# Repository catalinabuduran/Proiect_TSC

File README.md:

# OpenBook - Open Source e-Book Reader

## Functionalitate hardware

Dispozitivul OpenBook integreaza o serie de module si componente menite sa ofere o experienta completa pentru citirea cartilor in format digital, precum si extinderea functiilor prin senzori si periferice externe. Hardware-ul este compus din mai multe blocuri functionale, fiecare avand rolul. Am integrat atat componente de interfata (buton, ecran), cat si senzori, circuite de alimentare si protectie.

### Componente principale:

## Dispozitivul este compus dintr-un set de componente atent alese pentru a oferi un echilibru perfect intre performanta, consum redus de energie si modularitate. ##
|  Componenta            | Descriere                                                      |
|---------------------------|----------------------------------------------------------------|
|ESP32-C6-WROOM-1-N8  | MCU principal cu WiFi 6, BLE 5.0, SPI, I2C, UART               |
|E-paper Display | Afisaj ultra-low power, interfata SPI                          |
|SD Card         | Stocare pentru fisiere e-book si configurari                   |
|NOR Flash 64MB  | Memorie suplimentara pentru firmware si date                   |
|RTC-DS3231SN | Ceas in timp real, exact si stabil                             |
|    BME688   | Senzor de mediu complet: T, RH, presiune, VOC                  |
| MAX17048    | Masurare SoC baterie, tensiune, temperatura                  |
|MCP73831     | Incarcare LiPo simpla si eficienta                           |
|XC6220 LDO      | Regulare 5V -> 3.3V cu zgomot scazut                            |
|USB-C           | Alimentare + flash firmware + protectie ESD                   |
|Qwiic/Stemma QT | Extensie rapida pentru senzori I2C                            |

---

## Pinout ESP32-C6

Mai jos este un rezumat al pinilor folositi pe microcontroller, cu functiile si componenta asociata:

| GPIO  | Componenta        | Functie                     |
|--------|--------------------|-----------------------------|
| EN     | Buton Reset        | Reset hardware              |
| IO0    | RTC                | INT_RTC (interupt RTC)      |
| IO1    | RTC                | 32KHz output                |
| IO2    | SD Card            | MISO                        |
| IO3    | E-paper Display    | EPD_BUSY                    |
| IO4    | SD Card            | SS_SD (chip select)         |
| IO5    | E-paper Display    | EPD_DC                      |
| IO6    | SPI Shared         | SCK                         |
| IO7    | SPI Shared         | MOSI                        |
| IO8    | GPIO               | Utilizare generica          |
| IO9    | Boot Button        | Mod programare              |
| IO10   | E-paper Display    | EPD_CS                      |
| IO11   | NOR Flash          | FLASH_CS                    |
| IO12   | USB Interface      | USB_D-                      |
| IO13   | USB Interface      | USB_D+                      |
| IO15   | Buton Change       | Detectare schimbare         |
| IO16   | UART               | TX (debug serial)           |
| IO17   | UART               | RX (debug serial)           |
| IO18   | RTC                | RTC_RST                     |
| IO19   | MAX17048           | I2C_PW (alimentare I2C)     |
| IO20   | E-paper Display    | EPD_3V3_C (power control)   |
| IO21   | I2C Shared         | SDA                         |
| IO22   | I2C Shared         | SCL                         |
| IO23   | E-paper Display    | EPD_RST                     |

---

## Arhitectura si comunicatii

- **SPI Bus** este partajat intre: SD Card, E-paper Display, NOR Flash
- **I2C Bus** este partajat intre: RTC, BME688, MAX17048, Qwiic port
- **UART** este utilizat pentru debugging (TX/RX)
- **USB-C** foloseste GPIO dedicate pentru DP/DM si incarcare

---

# BOM TSC - Lista de componente

| Nr. piesa | Nume piesa | Site | Datasheet |
| --- | --- | --- | --- |
| 1 | BOOT_BUTON | https://www.snapeda.com/parts/EVQP7L01P/Panasonic%20Electronic%20Components/view-part/?welcome=home | https://www.snapeda.com/parts/EVQP7L01P/Panasonic/datasheet/ |
| 2 | C1, C1_BAT, C1_BAT2, C2,C2_BAT,C3,C4,C4_USB, C5, C5_USB, C6, C7, C8, C9,C10 | https://componentsearchengine.com/part-view/CC0402MRX5R5BB106/YAGEO | https://componentsearchengine.com/Datasheets/2/CC0402MRX5R5BB106.pdf |
| 3 | C10_SUPERCAR | https://industry.panasonic.com/global/en/products/control/switch/light-touch/number/evqpuj02k | https://industry.panasonic.com/global/en/downloads?tab=catalog&small_g_cd=203&part_no=EVQPUJ02K |
| 4 | CHANGE_BUTTON | https://www.snapeda.com/parts/EVQP7L01P/Panasonic%20Electronic%20Components/view-part/?welcome=home | https://www.snapeda.com/parts/EVQP7L01P/Panasonic/datasheet/ |
| 5 | C_DELAY | https://componentsearchengine.com/part-view/CC0402MRX5R5BB106/YAGEO | https://componentsearchengine.com/Datasheets/2/CC0402MRX5R5BB106.pdf |
| 6 | D1 | https://www.snapeda.com/parts/USBLC6-2SC6Y/STMicroelectronics/view-part/?ref=eda | https://www.snapeda.com/parts/USBLC6-2SC6Y/STMicroelectronics/view-part/?ref=eda |
| 7 | EPD_C1,EPD_C2, EPD_C3, EPD_C4, EPD_C5,EPD_C6,EPD_C7,EPD_C8,EPD_C9,EPD_C10,EPD_C11,EPD_C12 | https://componentsearchengine.com/part-view/CC0402MRX5R5BB106/YAGEO | https://componentsearchengine.com/Datasheets/2/CC0402MRX5R5BB106.pdf |
| 8 | IC1 | https://componentsearchengine.com/part-view/BD5229G-TR/ROHM%20Semiconductor | https://datasheet.datasheetarchive.com/originals/distributors/Datasheets_SAMA/f2b9741ef86007909f138d561a359946.pdf |
| 9 | IC4 | https://componentsearchengine.com/part-view/XC6220A331MR-G/Torex | https://product.torexsemi.com/system/files/series/xc6220.pdf |
| 10 | J1 | https://componentsearchengine.com/part-view/FH34SRJ-24S-0.5SH(99)/Hirose | https://www.hirose.com/en/product/document?clcode=CL0580-1255-6-99&productname=FH34SRJ-24S-0.5SH(99)&series=FH34SRJ&documenttype=2DDrawing&lang=en&documentid=0000990903 |
| 11 | J2 | https://componentsearchengine.com/part-view/USB4110-GF-A/GCT%20(GLOBAL%20CONNECTOR%20TECHNOLOGY) | https://gct.co/files/drawings/usb4110.pdf |
| 12 | J3,J4 | https://www.snapeda.com/parts/PRT-14417/SparkFun/view-part/ | https://www.snapeda.com/parts/PRT-14417/SparkFun%20Electronics/datasheet/ |
| 13 | MCP73831 | https://ro.mouser.com/ProductDetail/Microchip-Technology/MCP73831T-2ACI-OT?qs=yUQqVecv4qvbBQBGbHx0Mw%3D%3D&utm_id=20109199409&utm_source=google&utm_medium=cpc&utm_marketing_tactic=emeacorp&gad_source=1&gbraid=0AAAAADn_wf0-USzm1eg1ywGvQg_qMgG3H | https://ro.mouser.com/datasheet/2/268/MCP73831_Family_Data_Sheet_DS20001984H-3441711.pdf |
| 14 | L1 | https://ro.mouser.com/ProductDetail/Wurth-Elektronik/744043680?qs=PGXP4M47uW6VkZq%252BkzjrHA%3D%3D | https://www.we-online.com/components/products/datasheet/744043680.pdf |
| 15 | PFMF.050.1 | https://ro.mouser.com/ProductDetail/EPCOS-TDK/B72520T0350K062?qs=dEfas%2FXlABIszF52uu7vrg%3D%3D | https://www.tdk-electronics.tdk.com/inf/75/db/CTVS_14/Surge_protection_series.pdf |
| 16 | Q1,Q2 | https://componentsearchengine.com/part-view/DMG2305UX-7/Diodes%20Incorporated | https://www.diodes.com//assets/Datasheets/DMG2305UX.pdf |
| 17 | Q3 | https://componentsearchengine.com/part-view/SI1308EDL-T1-GE3/Vishay | https://componentsearchengine.com/part-view/SI1308EDL-T1-GE3/Vishay |
| 18 | Rezistente | https://componentsearchengine.com/part-view/R0402%201%25%20100%20K%20(RC0402FR-07100KL)/YAGEO | https://www.yageo.com/upload/media/product/products/datasheet/rchip/PYu-RC_Group_51_RoHS_L_12.pdf |
| 19 | RESET_BUTTON | https://www.snapeda.com/parts/EVQP7L01P/Panasonic%20Electronic%20Components/view-part/?welcome=home | https://www.snapeda.com/parts/EVQP7L01P/Panasonic/datasheet/ |
| 20 | R_BOOT | https://componentsearchengine.com/part-view/R0402%201%25%20100%20K%20(RC0402FR-07100KL)/YAGEO | https://www.yageo.com/upload/media/product/products/datasheet/rchip/PYu-RC_Group_51_RoHS_L_12.pdf |
| 21 | R_CAPACITOR | https://componentsearchengine.com/part-view/R0402%201%25%20100%20K%20(RC0402FR-07100KL)/YAGEO | https://www.yageo.com/upload/media/product/products/datasheet/rchip/PYu-RC_Group_51_RoHS_L_12.pdf |
| 22 | R_CHANGE | https://componentsearchengine.com/part-view/R0402%201%25%20100%20K%20(RC0402FR-07100KL)/YAGEO | https://www.yageo.com/upload/media/product/products/datasheet/rchip/PYu-RC_Group_51_RoHS_L_12.pdf |
| 23 | R_CL1 | https://componentsearchengine.com/part-view/R0402%201%25%20100%20K%20(RC0402FR-07100KL)/YAGEO | https://www.yageo.com/upload/media/product/products/datasheet/rchip/PYu-RC_Group_51_RoHS_L_12.pdf |
| 24 | R_RESET | https://componentsearchengine.com/part-view/R0402%201%25%20100%20K%20(RC0402FR-07100KL)/YAGEO | https://www.yageo.com/upload/media/product/products/datasheet/rchip/PYu-RC_Group_51_RoHS_L_12.pdf |
| 26 | SENSOR2 | https://www.snapeda.com/parts/BME680/Bosch/view-part/?welcome=home | https://www.snapeda.com/parts/BME680/Bosch%20Sensortec/datasheet/ |
| 27 | SJ1 | https://grabcad.com/library/solder-jumpers-1 | https://grabcad.com/library/solder-jumpers-1 |
| 28 | U1 | https://www.snapeda.com/parts/W25Q512JVEIQ/Winbond+Electronics/view-part/?ref=eda | https://www.snapeda.com/parts/W25Q512JVEIQ/Winbond+Electronics/view-part/?ref=eda |
| 29 | U2 | https://www.snapeda.com/parts/ESP32-C6-WROOM-1-N8/Espressif+Systems/view-part/?ref=eda | https://www.snapeda.com/parts/ESP32-C6-WROOM-1-N8/Espressif%20Systems/datasheet/ |
| 30 | U3 | https://www.snapeda.com/parts/DS3231SN%23/Analog+Devices/view-part/?ref=eda | https://www.snapeda.com/parts/DS3231SN%23/Analog%20Devices/datasheet/ |
| 31 | U4 | https://www.snapeda.com/parts/MAX17048G+T10/Analog+Devices/view-part/?ref=eda | https://www.snapeda.com/parts/MAX17048G+T10/Analog%20Devices/datasheet/ |
| 32 | TP-uri | Le-am desenat manual |  |

3D Design

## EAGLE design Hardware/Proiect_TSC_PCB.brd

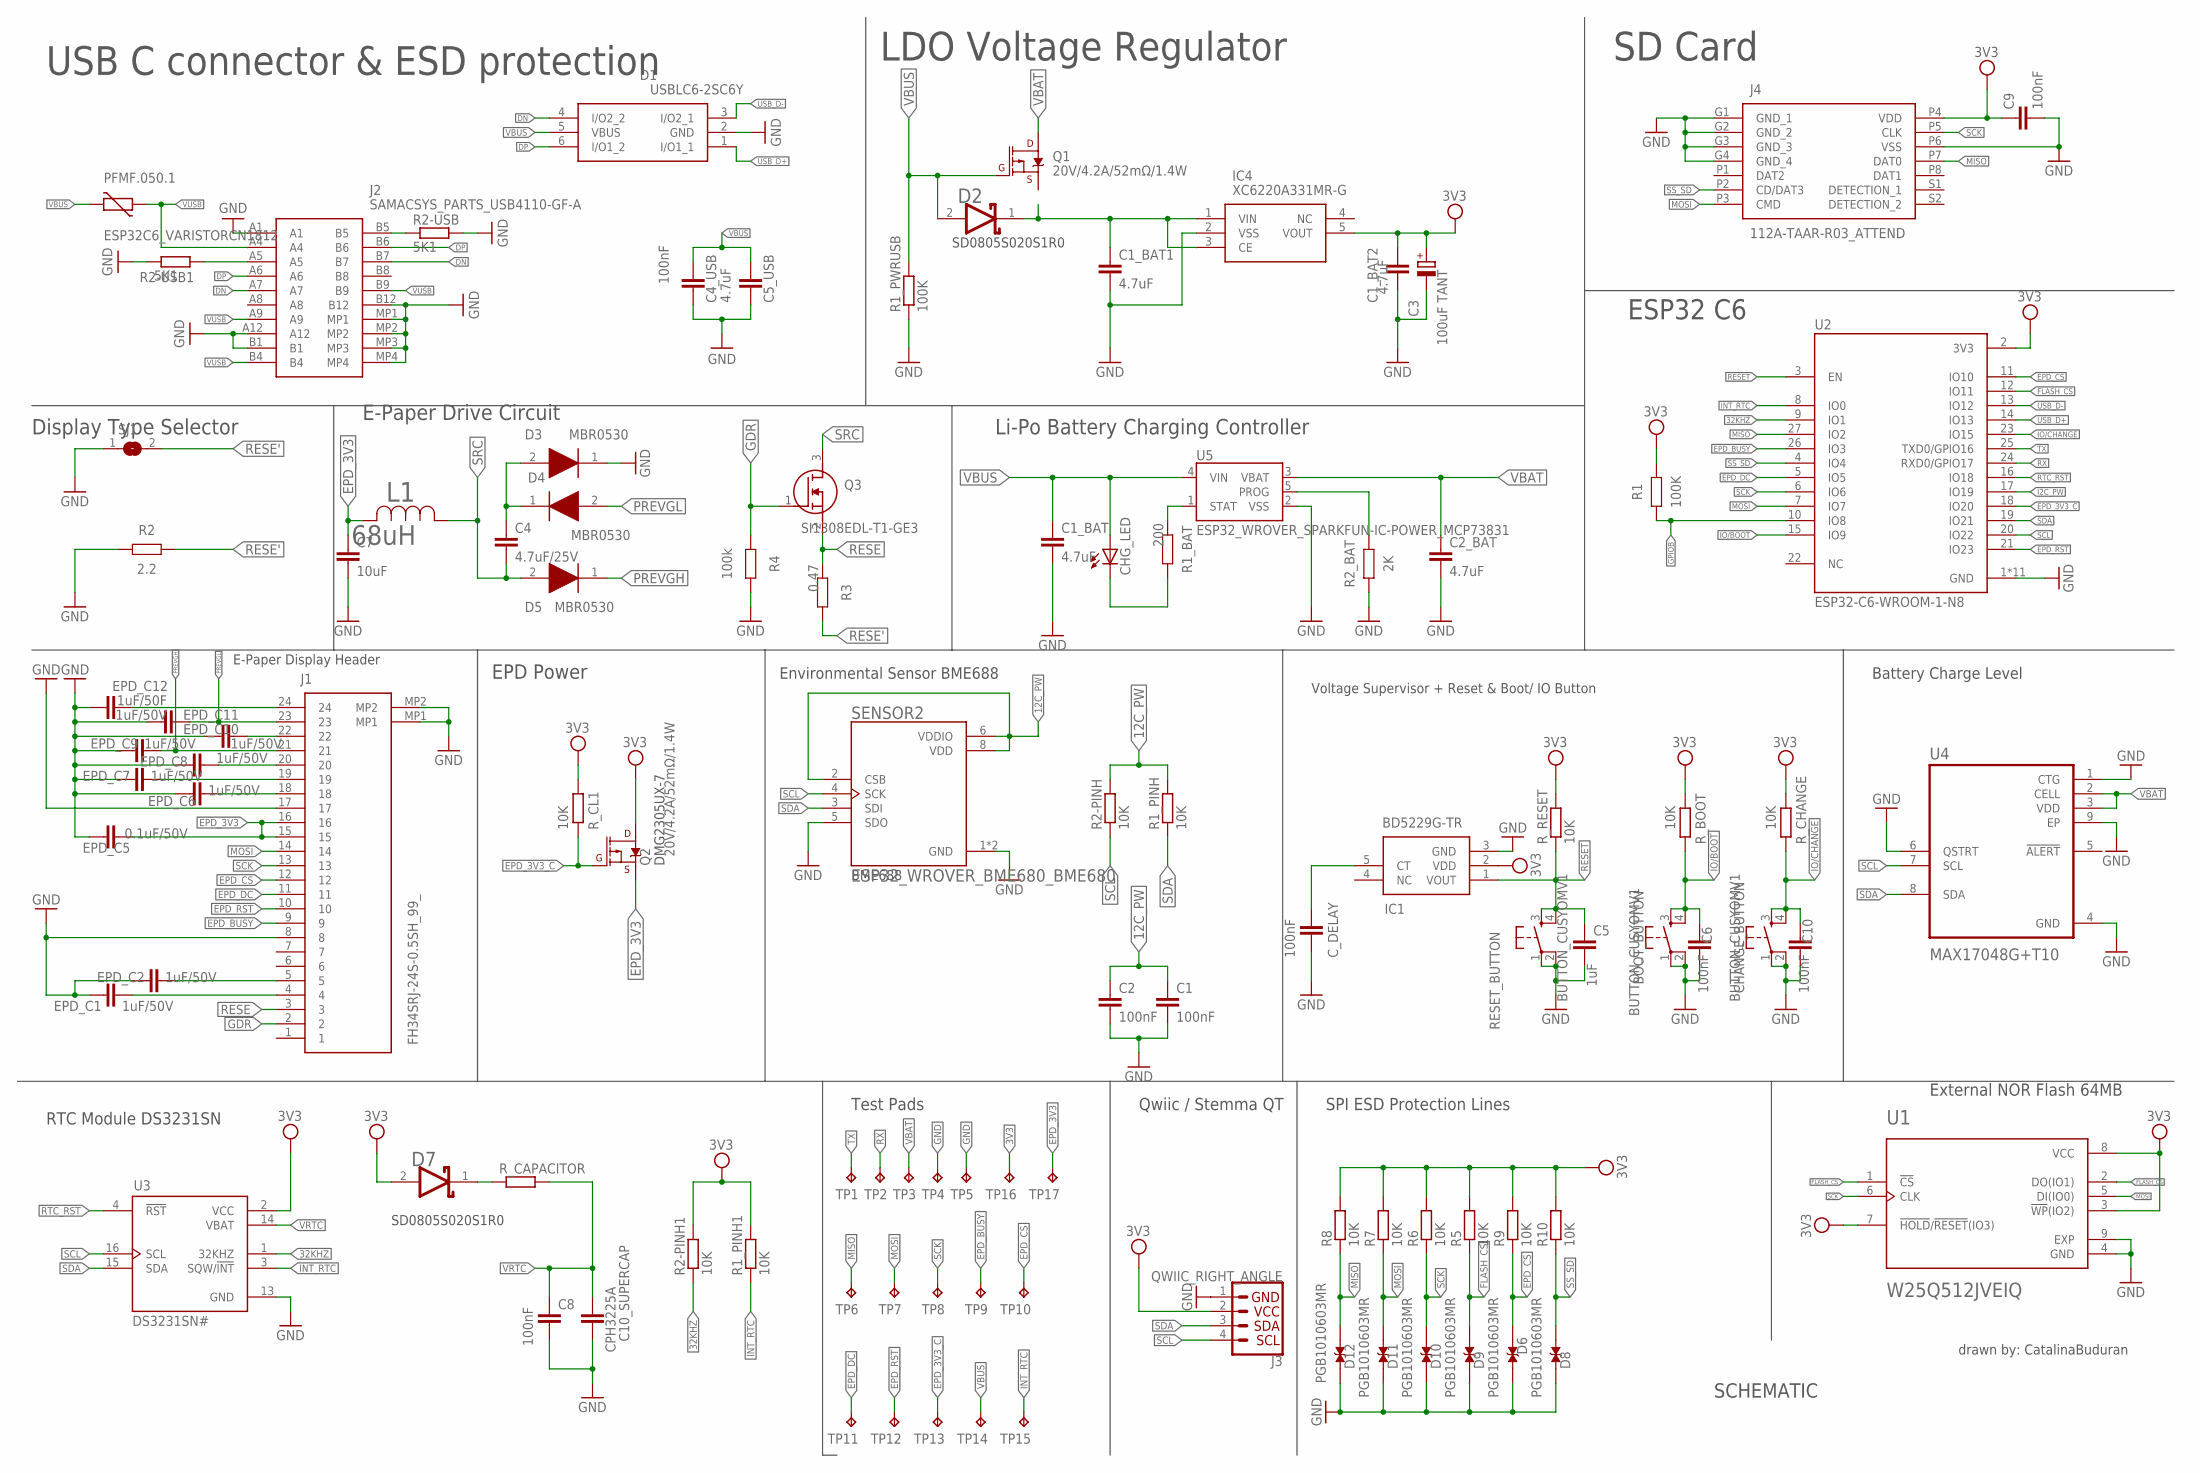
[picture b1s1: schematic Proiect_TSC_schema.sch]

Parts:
BOOT_BUTTON: BUTTON_CUSYOMV1; MYBUTTON
C1, C2, C4_USB, C6, C9, C10: 100nF; ESP32_WROVER_EAGLE-LTSPICE_C0402
C1_BAT, C1_BAT1, C1_BAT2, C2_BAT, C5_USB: 4.7uF; ESP32_WROVER_EAGLE-LTSPICE_C0402
C3: 100uF TANT; RCL_CT3528
C4: 4.7uF/25V; ESP32_WROVER_EAGLE-LTSPICE_C0402
C5: 1uF; EAGLE-LTSPICE_C0402
C7: 10uF; ESP32_WROVER_EAGLE-LTSPICE_C0402
C8: 100nF; EAGLE-LTSPICE_C0402
C10_SUPERCAP: CPH3225A; EAGLE-LTSPICE_C0402
CHANGE_BUTTON: BUTTON_CUSYOMV1; MYBUTTON
CHG_LED: ADAFRUIT_LEDCHIP-LED0603; ADAFRUIT_CHIP-LED0603
C_DELAY: 100nF; ESP32_WROVER_EAGLE-LTSPICE_C0402
D1: USBLC6-2SC6Y; SOT95P280X145-6N
D2, D7: ESP32_WROVER_AVX---SD0805S020S1R0_AVX_SD0805S020S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; ESP32_WROVER_AVX---SD0805S020S1R0_AVX_SD0805S020S1R0_0
D3, D4, D5: MBR0530; SOD3716X135N
D6, D8, D9, D10, D11, D12: PGB1010603MR; DIOC1608X36N
EPD_C1, EPD_C2, EPD_C6, EPD_C7, EPD_C8, EPD_C9, EPD_C10, EPD_C11: 1uF/50V; ESP32_WROVER_EAGLE-LTSPICE_C0402
EPD_C5: 0.1uF/50V; ESP32_WROVER_EAGLE-LTSPICE_C0402
EPD_C12: 1uF/50F; ESP32_WROVER_EAGLE-LTSPICE_C0402
IC1: BD5229G-TR; SOT95P280X125-5N
IC4: XC6220A331MR-G; SOT95P280X120-5N
J1: FH34SRJ-24S-0.5SH_99_; FH34SRJ24S05SH99
J2: SAMACSYS_PARTS_USB4110-GF-A; SAMACSYS_PARTS_USB4110GFA
J3: QWIIC_RIGHT_ANGLE; JST04_1MM_RA
J4: 112A-TAAR-R03_ATTEND; 112ATAARR03ATTEND
L1: 68uH; IND_4828-WE-TPC_WRE
PFMF.050.1: ESP32C6_VARISTORCN1812; ESP32C6_VARISTOR_CT/CN1812
Q1, Q2: 20V/4.2A/52mΩ/1.4W; ESP32_WROVER_SPARKFUN-DISCRETESEMI_SOT23-3
Q3: SI1308EDL-T1-GE3; SOT65P210X110-3N
R1: 100K; RESC1005X40
R1_BAT: 200; RESC1005X40
R1_PINH, R1_PINH1, R2-PINH, R2-PINH1, R5, R6, R7, R8, R9, R10: 10K; ESP32_WROVER_EAGLE-LTSPICE_R0402
R1_PWRUSB: 100K; ESP32_WROVER_EAGLE-LTSPICE_R0402
R2: 2.2; RESC1005X40
R2-USB, R2-USB1: 5K1; ESP32_WROVER_EAGLE-LTSPICE_R0402
R2_BAT: 2K; RESC1005X40
R3: 0.47; RESC1005X40
R4: 100k; RESC1005X40
RESET_BUTTON: BUTTON_CUSYOMV1; MYBUTTON
R_BOOT: 10K; ESP32_WROVER_EAGLE-LTSPICE_R0402
R_CAPACITOR: ESP32_WROVER_EAGLE-LTSPICE_RR0402; ESP32_WROVER_EAGLE-LTSPICE_R0402
R_CHANGE: 10K; ESP32_WROVER_EAGLE-LTSPICE_R0402
R_CL1: 10K; ESP32_WROVER_EAGLE-LTSPICE_R0402
R_RESET: 10K; ESP32_WROVER_EAGLE-LTSPICE_R0402
SENSOR2: ESP32_WROVER_BME680_BME680; ESP32_WROVER_BME680_PSON80P300X300X100-8N
SJ1: SJ
TP1, TP2, TP3, TP4, TP5, TP6, TP7, TP8, TP9, TP10, TP11, TP12, TP13, TP14, TP15, TP16, TP17: TPTP20R; TP20R
U1: W25Q512JVEIQ; SON127P600X800X80-9N
U2: ESP32-C6-WROOM-1-N8; XCVR_ESP32-C6-WROOM-1-N8
U3: DS3231SN#; SOIC127P1032X265-16N
U4: MAX17048G+T10; SON50P200X200X80-9N
U5: ESP32_WROVER_SPARKFUN-IC-POWER_MCP73831; ESP32_WROVER_SPARKFUN-IC-POWER_SOT23-5

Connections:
3V3: C1_BAT2.1, C3.+, C9.1, D7.2 (ANODE), IC1.2 (VDD), IC4.5 (VOUT), J3.2, J4.P4 (VDD), R1.2, R1_PINH1.2, R2-PINH1.2, R5.2, R6.2, R7.2, R8.2, R9.2, R10.2, R_BOOT.2, R_CHANGE.2, R_CL1.2, TP16.TP, U1.3 (!WP!(IO2)), U1.7 (!HOLD!/!RESET!(IO3)), U1.8 (VCC), U2.2 (3V3), U3.2 (VCC)
12C_PW: C1.1, C2.1, R1_PINH.2, R2-PINH.2, SENSOR2.2 (CSB), SENSOR2.6 (VDDIO), SENSOR2.8 (VDD)
32KHZ: R2-PINH1.1, U2.9 (IO1), U3.1 (32KHZ)
DN: D1.4 (I/O2_2), J2.A7, J2.B7
DP: D1.6 (I/O1_2), J2.A6, J2.B6
EPD_3V3: C7.1, EPD_C5.2, J1.15, J1.16, L1.2, Q2.2 (S), TP17.TP
EPD_3V3_C: Q2.1 (G), R_CL1.1, TP13.TP, U2.18 (IO20)
EPD_BUSY: J1.9, TP9.TP, U2.26 (IO3)
EPD_CS: D6.2, J1.12, R9.1, TP10.TP, U2.11 (IO10)
EPD_DC: J1.11, TP11.TP, U2.5 (IO5)
EPD_RST: J1.10, TP12.TP, U2.21 (IO23)
FLASH_CS: D9.2, R5.1, U1.1 (!CS), U2.12 (IO11)
GDR: J1.2, Q3.1 (G), R4.2
GND: BOOT_BUTTON.1, BOOT_BUTTON.2, C1.2, C1_BAT.2, C1_BAT1.2, C1_BAT2.2, C2.2, C2_BAT.2, C3.-, C4_USB.2, C5.2, C5_USB.2, C6.2, C7.2, C8.2, C9.2, C10.2, C10_SUPERCAP.2, CHANGE_BUTTON.1, CHANGE_BUTTON.2, C_DELAY.2, D1.2 (GND), D3.1 (K), D6.1, D8.1, D9.1, D10.1, D11.1, D12.1, EPD_C5.1, EPD_C6.1, EPD_C7.1, EPD_C8.1, EPD_C9.1, EPD_C10.1, EPD_C11.1, EPD_C12.1, IC1.3 (GND), IC4.2 (VSS), J1.17, J2.A1, J2.A12, J2.B1, J2.B12, J2.MP1, J2.MP2, J2.MP3, J2.MP4, J3.1, J4.G1 (GND_1), J4.G2 (GND_2), J4.G3 (GND_3), J4.G4 (GND_4), J4.P6 (VSS), R1_PWRUSB.1, R2.1, R2-USB.2, R2-USB1.1, R2_BAT.1, RESET_BUTTON.1, RESET_BUTTON.2, SENSOR2.1 (GND), SENSOR2.5 (SDO), SENSOR2.7 (GND), TP4.TP, TP5.TP, U1.4 (GND), U1.9 (EXP), U2.1 (GND), U2.28 (GND), U2.29_1 (GND), U2.29_2 (GND), U2.29_3 (GND), U2.29_4 (GND), U2.29_5 (GND), U2.29_6 (GND), U2.29_7 (GND), U2.29_8 (GND), U2.29_9 (GND), U4.1 (CTG), U4.4 (GND), U4.6 (QSTRT), U4.9 (EP), U5.2 (VSS)
GPIOB: R1.1, U2.10 (IO8)
I2C_PW: U2.17 (IO19)
INT_RTC: R1_PINH1.1, TP15.TP, U2.8 (IO0), U3.3 (SQW/!INT)
IO/BOOT: BOOT_BUTTON.3, BOOT_BUTTON.4, C6.1, R_BOOT.1, U2.15 (IO9)
IO/CHANGE: C10.1, CHANGE_BUTTON.3, CHANGE_BUTTON.4, R_CHANGE.1, U2.23 (IO15)
MISO: D12.2, J4.P7 (DAT0), R8.1, TP6.TP, U2.27 (IO2)
MOSI: D11.2, J1.14, J4.P3 (CMD), R7.1, TP7.TP, U1.5 (DI(IO0)), U2.7 (IO7)
unnamed: J2.B5, R2-USB.1
unnamed: J2.A5, R2-USB1.2
unnamed: C1_BAT1.1, D2.1 (CATHODE), IC4.1 (VIN), IC4.3 (CE)
unnamed: R1_BAT.2, U5.1 (STAT)
unnamed: R2_BAT.2, U5.5 (PROG)
unnamed: C4.1, D3.2 (A), D4.1 (K)
unnamed: CHG_LED.C, R1_BAT.1
unnamed: J1.MP1, J1.MP2
unnamed: EPD_C1.2, J1.4
unnamed: EPD_C2.2, J1.5
unnamed: EPD_C1.1, EPD_C2.1, J1.8
unnamed: EPD_C6.2, J1.18
unnamed: EPD_C7.2, J1.19
unnamed: C_DELAY.1, IC1.5 (CT)
unnamed: EPD_C8.2, J1.20
unnamed: EPD_C10.2, J1.22
unnamed: EPD_C12.2, J1.24
unnamed: D7.1 (CATHODE), R_CAPACITOR.1
PREVGH: D5.1 (K), EPD_C9.2, J1.21
PREVGL: D4.2 (A), EPD_C11.2, J1.23
RESE: J1.3, Q3.2 (S), R3.2
RESE': R2.2, R3.1, SJ1.2
RESET: C5.1, IC1.1 (VOUT), RESET_BUTTON.3, RESET_BUTTON.4, R_RESET.1, U2.3 (EN)
RTC_RST: U2.16 (IO18), U3.4 (!RST)
RX: TP2.TP, U2.24 (RXD0/GPIO17)
SCK: D10.2, J1.13, J4.P5 (CLK), R6.1, TP8.TP, U1.6 (CLK), U2.6 (IO6)
SCL: J3.4, R2-PINH.1, SENSOR2.4 (SCK), U2.20 (IO22), U3.16 (SCL), U4.7 (SCL)
SDA: J3.3, R1_PINH.1, SENSOR2.3 (SDI), U2.19 (IO21), U3.15 (SDA), U4.8 (SDA)
SRC: C4.2, D5.2 (A), L1.1, Q3.3 (D)
SS_SD: D8.2, J4.P2 (CD/DAT3), R10.1, U2.4 (IO4)
TX: TP1.TP, U2.25 (TXD0/GPIO16)
USB_D+: D1.1 (I/O1_1), U2.14 (IO13)
USB_D-: D1.3 (I/O2_1), U2.13 (IO12)
VBAT: C2_BAT.1, Q1.3 (D), TP3.TP, U4.2 (CELL), U4.3 (VDD), U5.3 (VBAT)
VBUS: C1_BAT.1, C4_USB.1, C5_USB.1, CHG_LED.A, D1.5 (VBUS), D2.2 (ANODE), PFMF.050.1.2, Q1.1 (G), R1_PWRUSB.2, TP14.TP, U5.4 (VIN)
VRTC: C8.1, C10_SUPERCAP.1, R_CAPACITOR.2, U3.14 (VBAT)
VUSB: J2.A4, J2.A9, J2.B4, J2.B9, PFMF.050.1.1

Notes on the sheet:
DMG2305UX-7
BME688
SCHEMATIC
drawn by: CatalinaBuduran
USB C connector & ESD protection
LDO Voltage Regulator
SD Card
Display Type Selector
E-Paper Drive Circuit
Li-Po Battery Charging Controller
ESP32 C6
E-Paper Display Header
EPD Power
Environmental Sensor BME688
Voltage Supervisor + Reset & Boot/ IO Button
Battery Charge Level
RTC Module DS3231SN
Test Pads
Qwiic / Stemma QT
SPI ESD Protection Lines
External NOR Flash 64MB
SD0805S020S1R0

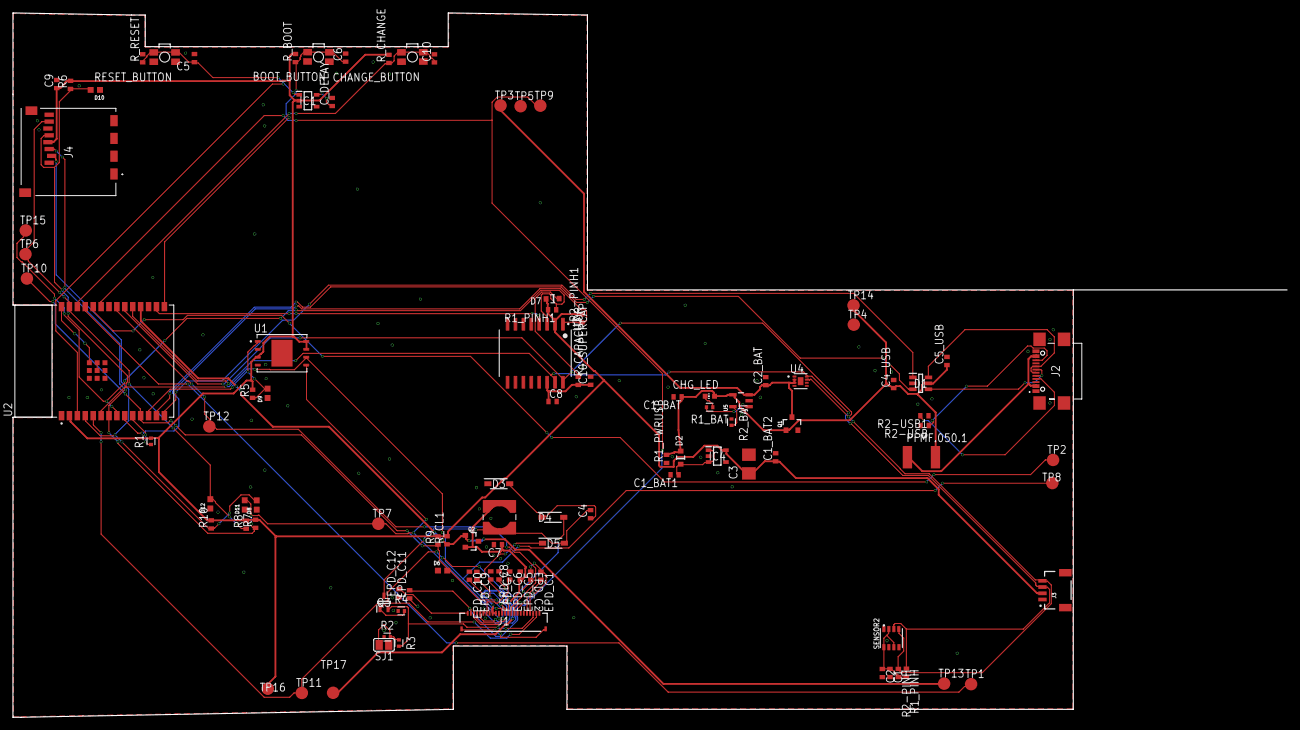
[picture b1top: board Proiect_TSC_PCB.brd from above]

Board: 2 copper layers, 170.2 x 113.0 mm, 103 parts (0 on the bottom side), 57 nets.

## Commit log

2025-04-06 Add files via upload
    Schema+PCB
2025-04-06 Add files via upload
    Gerbers+BOM+PAP
2025-04-06 Add files via upload
    exploded view (.step) + fișierul 3D Fusion360 cu dispozitivul complet
2025-04-06 Add files via upload
    Diagrama
2025-04-06 Create LICENSE
2025-04-14 Add files via upload
    Update diagram
2025-04-14 Add files via upload
    Update README
2025-04-15 Update schematic and PCB
2025-04-15 Update 3D

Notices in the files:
parts and their libraries:
COPYRIGHT: Copyright (C) 2024 Ultra Librarian. All rights reserved.
